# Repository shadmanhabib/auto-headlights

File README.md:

# Auto-Headlights
Controller designed to control and automate vehicle headlights based on environmental conditions in parallel with vehicle controls.

## Table of Contents
- [Auto-Headlights](#Auto-Headlights)
  - [Table of Contents](#table-of-contents)
  - [About The Project](#about-the-project)
  - [Getting Started](#getting-started)
    - [Prerequisites](#prerequisites)
    - [Installation](#installation)
  - [Usage](#usage)
  - [Changelog](#changelog)

## About The Project
This project was designed for a Subaru Liberty/Legacy 4GEN in an effort to add modern automatic headlights and light home functionalities.

It involves PCB design and automotive wiring. Hence, this project should only be replicated by individuals who are confident with automotive electrical systems.

The design was based around the following requirements:

1. Control headlights dependent on light conditions.
2. Ensure original vehicle controls remained functional.
3. Support reading lock/unlock states.
4. Ability to update software i.e. ensure programing pins are accessible through header/connector.

## Getting Started
To get a build this project (or parts thereof), these steps may be followed.

### Prerequisites
1. PlatformIO is required to build binaries from source code. Microchip Studios or Arduino IDE can also be used but will require extra configuration.
2. An ISP programmer is required to upload to the controller. An Arduino as ISP can be used.
3. If you want to make changes to the PCB design or would like to generate new fabrication files, an installation of KiCAD is required.
4. A 3D printer is required to fabricate the PCB enclosure from the provided CAD files.

### Installation
1. Manufacture and assemble controller PCB.
2. Build and upload code binary.
3. Fabricate PCB enclosure.
4. Splice vehicle wiring as per wiring diragram/requirements.
5. Pin connectors and attach to controller.
6. Mount controller in a secure location.

## Usage
Examples will be given in future iterations of this file.

_For more examples, please refer to the [Documentation](https://)_

## Changelog
All notable changes to this project will be documented in this section.

The format is based on [Keep a Changelog](https://keepachangelog.com/en/1.0.0/),
and this project attempts to adhere to [Semantic Versioning](https://semver.org/spec/v2.0.0.html).

### [v1.0.0]
#### Initial design
- ATmega328PB based design.
- Included optocouplers to read 12V signals from vehicle.
- MOLEX Micro-fit connectors.

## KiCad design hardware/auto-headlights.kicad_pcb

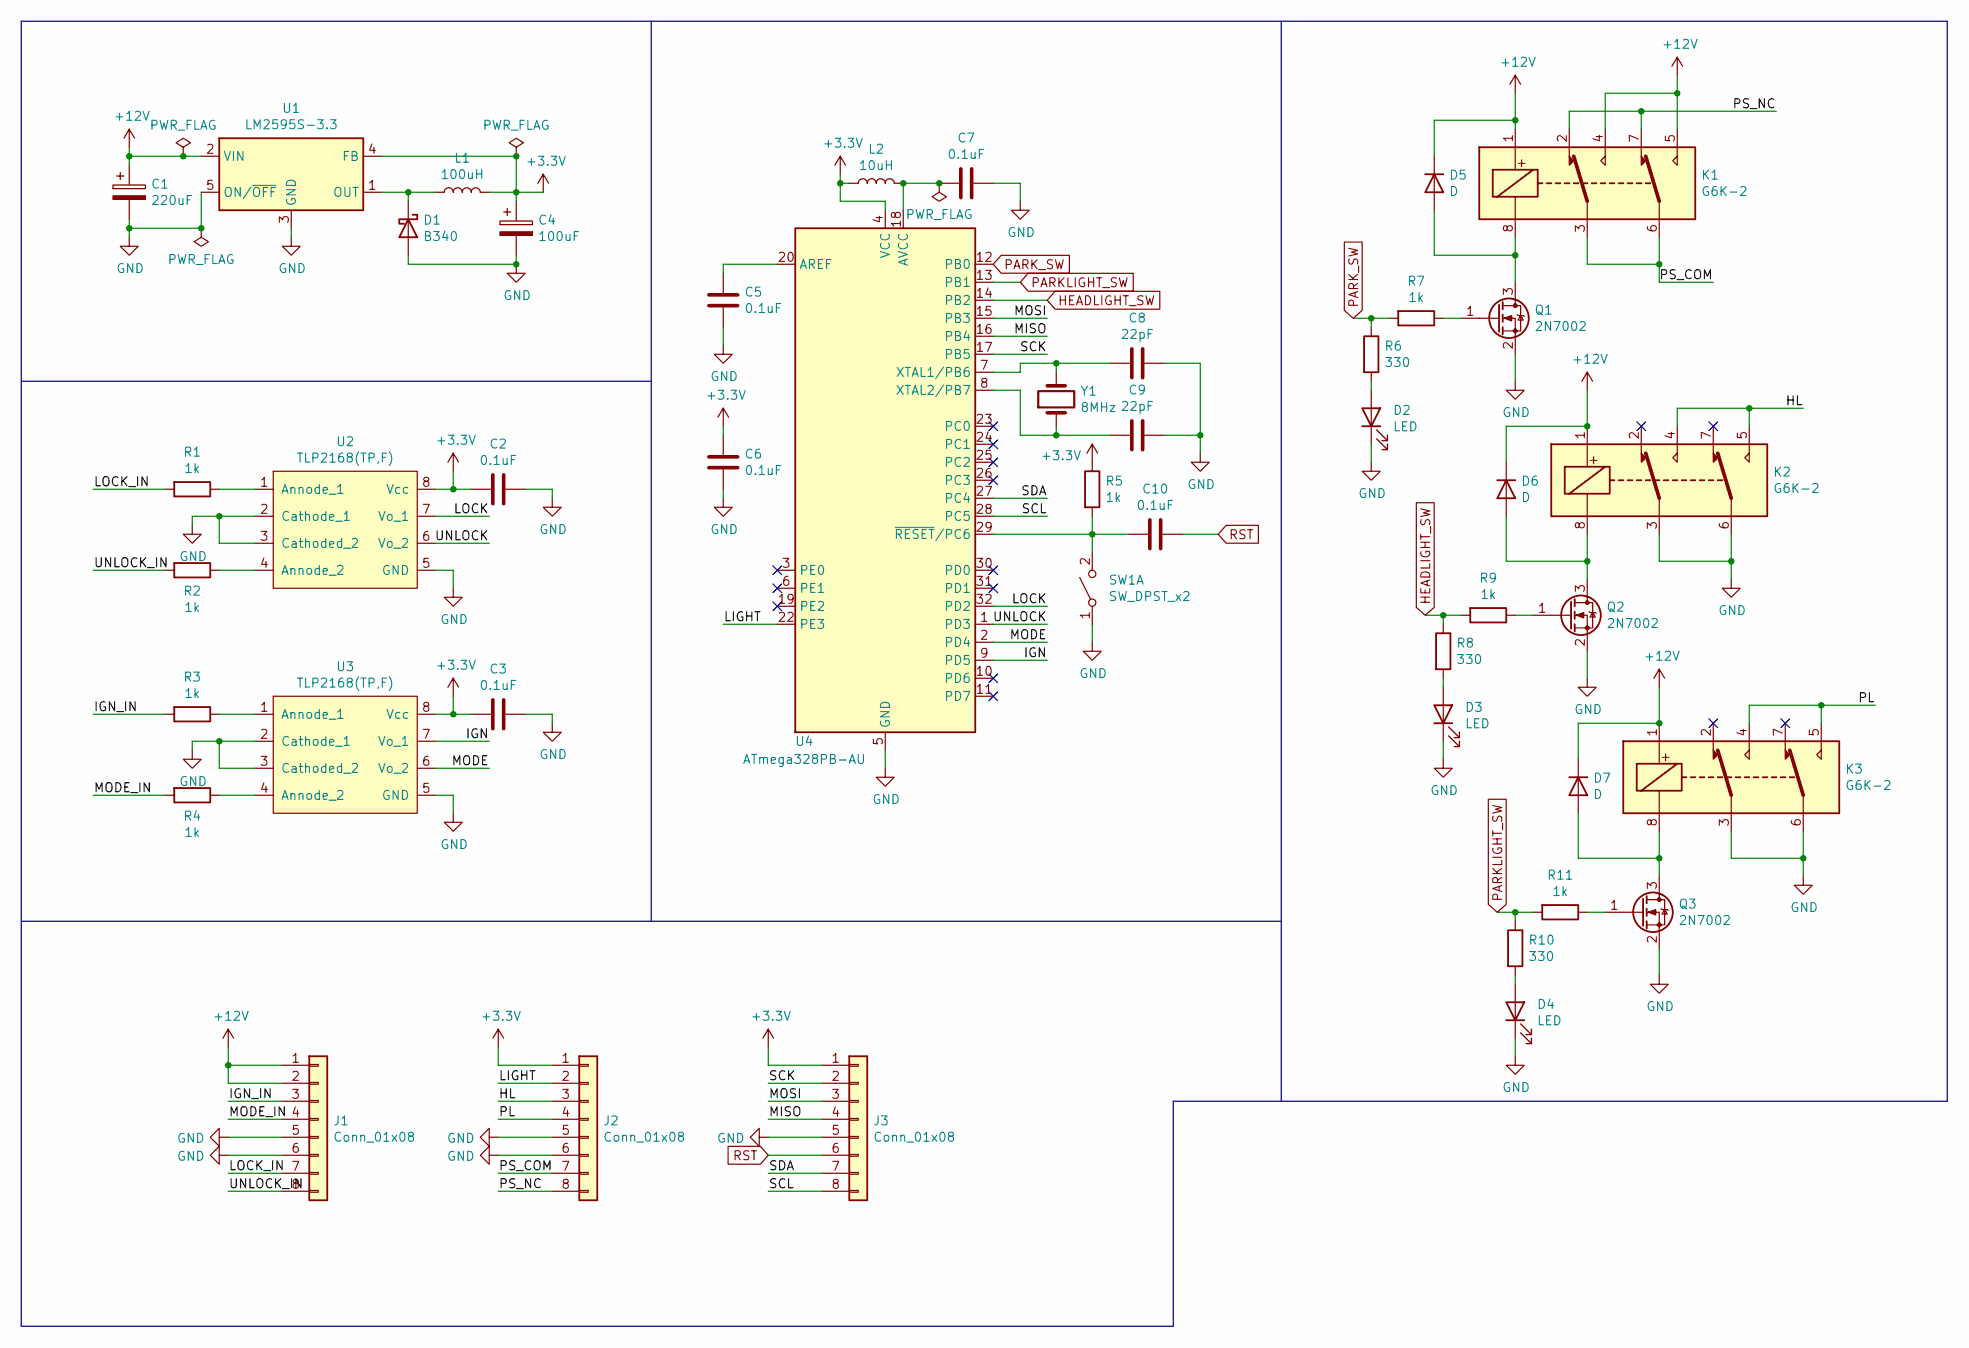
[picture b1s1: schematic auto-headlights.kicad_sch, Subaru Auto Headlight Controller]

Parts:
C1: 220uF; CP_EIA-7343-31_Kemet-D
C2, C3, C5, C6, C7, C10: 0.1uF; C_0805_2012Metric
C4: 100uF; CP_EIA-3528-21_Kemet-B
C8, C9: 22pF; C_0805_2012Metric
D1: B340; D_SOD-123
D2, D3, D4: LED; LED_0805_2012Metric_Castellated
D5, D6, D7: D; D_SOD-123
J1, J2, J3: Conn_01x08; Molex_Micro-Fit_3.0_43045-0812_2x04_P3.00mm_Vertical
K1, K2, K3: G6K-2; Relay_DPDT_Omron_G6K-2F-Y
L1: 100uH; L_0805_2012Metric
L2: 10uH; L_0805_2012Metric
Q1, Q2, Q3: 2N7002; SOT-23
R1, R2, R3, R4, R5, R7, R9, R11: 1k; R_0805_2012Metric
R6, R8, R10: 330; R_0805_2012Metric
SW1: SW_DPST_x2; SW_SPST_Omron_B3FS-100xP
U1: LM2595S-3.3; TO-263-5_TabPin3
U2, U3: TLP2168(TP,F); SO-8_3.9x4.9mm_P1.27mm
U4: ATmega328PB-AU; TQFP-32_7x7mm_P0.8mm
Y1: 8MHz; Crystal_SMD_5032-2Pin_5.0x3.2mm

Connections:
+3V3: C2.2, C3.2, C4.1, C6.1, J2.1, J3.1, L1.2, L2.1, R5.1, U1.4 (FB), U2.8 (Vcc), U3.8 (Vcc), U4.4 (VCC)
+12V: C1.1, D5.1 (K), D6.1 (K), D7.1 (K), J1.1, J1.2, K1.1, K1.4, K1.5, K2.1, K3.1, U1.2 (VIN)
/HL: J2.3, K2.4, K2.5
/IGN: U3.7 (Vo_1), U4.9 (PD5)
/IGN_IN: J1.3, R3.2
/LIGHT: J2.2, U4.22 (PE3)
/LOCK: U2.7 (Vo_1), U4.32 (PD2)
/LOCK_IN: J1.7, R1.2
/MISO: J3.4, U4.16 (PB4)
/MODE: U3.6 (Vo_2), U4.2 (PD4)
/MODE_IN: J1.4, R4.2
/MOSI: J3.3, U4.15 (PB3)
/PL: J2.4, K3.4, K3.5
/PS_COM: J2.7, K1.3, K1.6
/PS_NC: J2.8, K1.2, K1.7
/SCK: J3.2, U4.17 (PB5)
/SCL: J3.8, U4.28 (PC5)
/SDA: J3.7, U4.27 (PC4)
/UNLOCK: U2.6 (Vo_2), U4.1 (PD3)
/UNLOCK_IN: J1.8, R2.2
GND: C1.2, C2.1, C3.1, C4.2, C5.2, C6.2, C7.1, C8.1, C9.1, D1.2 (A), D2.1 (K), D3.1 (K), D4.1 (K), J1.5, J1.6, J2.5, J2.6, J3.5, K2.3, K2.6, K3.3, K3.6, Q1.2 (S), Q2.2 (S), Q3.2 (S), SW1.1 (A), U1.3 (GND), U1.5 (ON/~OFF), U2.2 (Cathode_1), U2.3 (Cathoded_2), U2.5 (GND), U3.2 (Cathode_1), U3.3 (Cathoded_2), U3.5 (GND), U4.5 (GND), U4.21 (GND)
HEADLIGHT_SW: R8.1, R9.2, U4.14 (PB2)
unnamed: C5.1, U4.20 (AREF)
unnamed: C7.2, L2.2, U4.18 (AVCC)
unnamed: C8.2, U4.7 (XTAL1/PB6), Y1.2
unnamed: C9.2, U4.8 (XTAL2/PB7), Y1.1
unnamed: C10.2, R5.2, SW1.2 (B), U4.29 (~RESET/PC6)
unnamed: D1.1 (K), L1.1, U1.1 (OUT)
unnamed: D2.2 (A), R6.2
unnamed: D3.2 (A), R8.2
unnamed: D4.2 (A), R10.2
unnamed: D5.2 (A), K1.8, Q1.3 (D)
unnamed: D6.2 (A), K2.8, Q2.3 (D)
unnamed: D7.2 (A), K3.8, Q3.3 (D)
unnamed: Q1.1 (G), R7.1
unnamed: Q2.1 (G), R9.1
unnamed: Q3.1 (G), R11.1
unnamed: R1.1, U2.1 (Annode_1)
unnamed: R2.1, U2.4 (Annode_2)
unnamed: R3.1, U3.1 (Annode_1)
unnamed: R4.1, U3.4 (Annode_2)
PARKLIGHT_SW: R10.1, R11.2, U4.13 (PB1)
PARK_SW: R6.1, R7.2, U4.12 (PB0)
RST: C10.1, J3.6

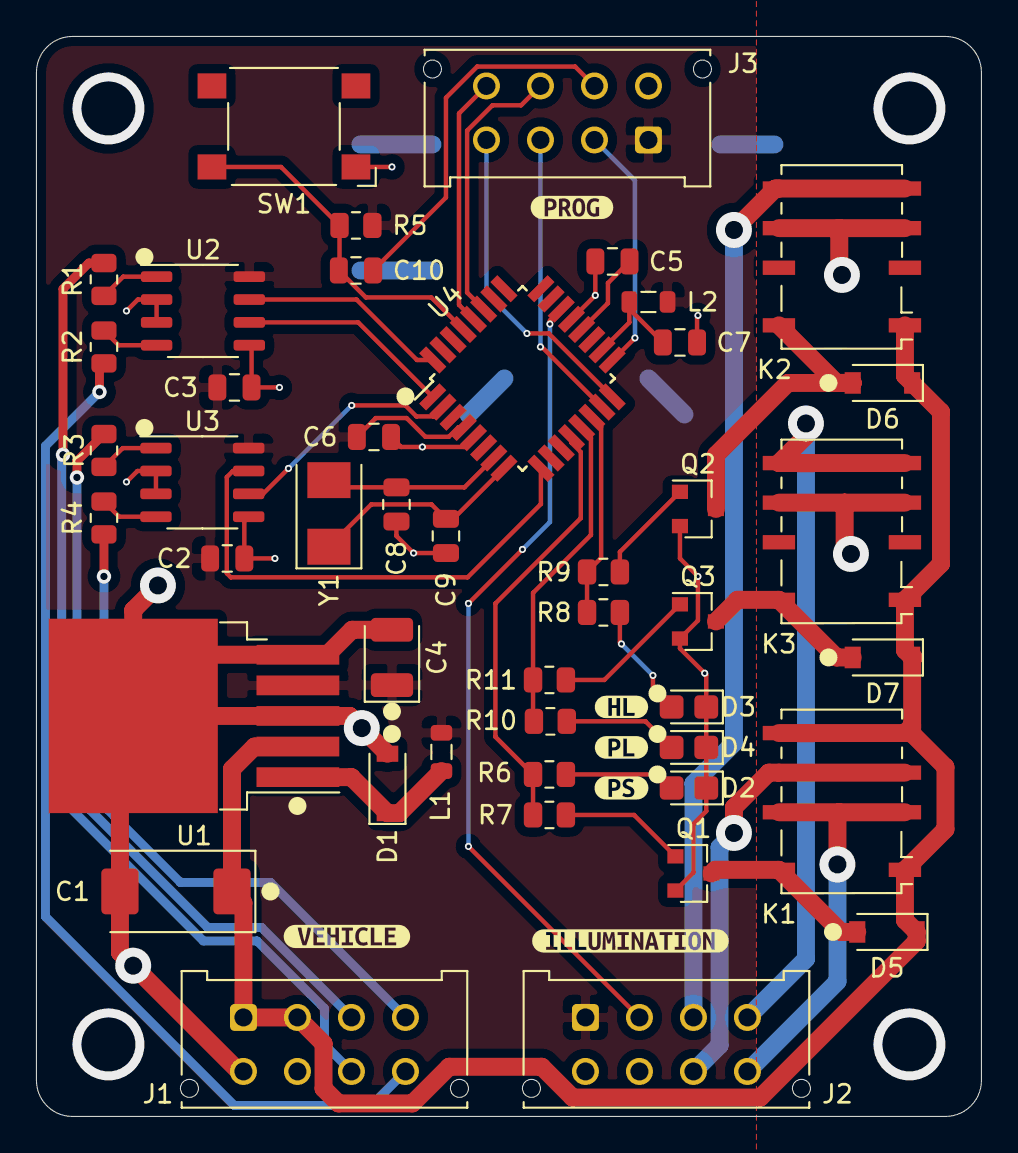
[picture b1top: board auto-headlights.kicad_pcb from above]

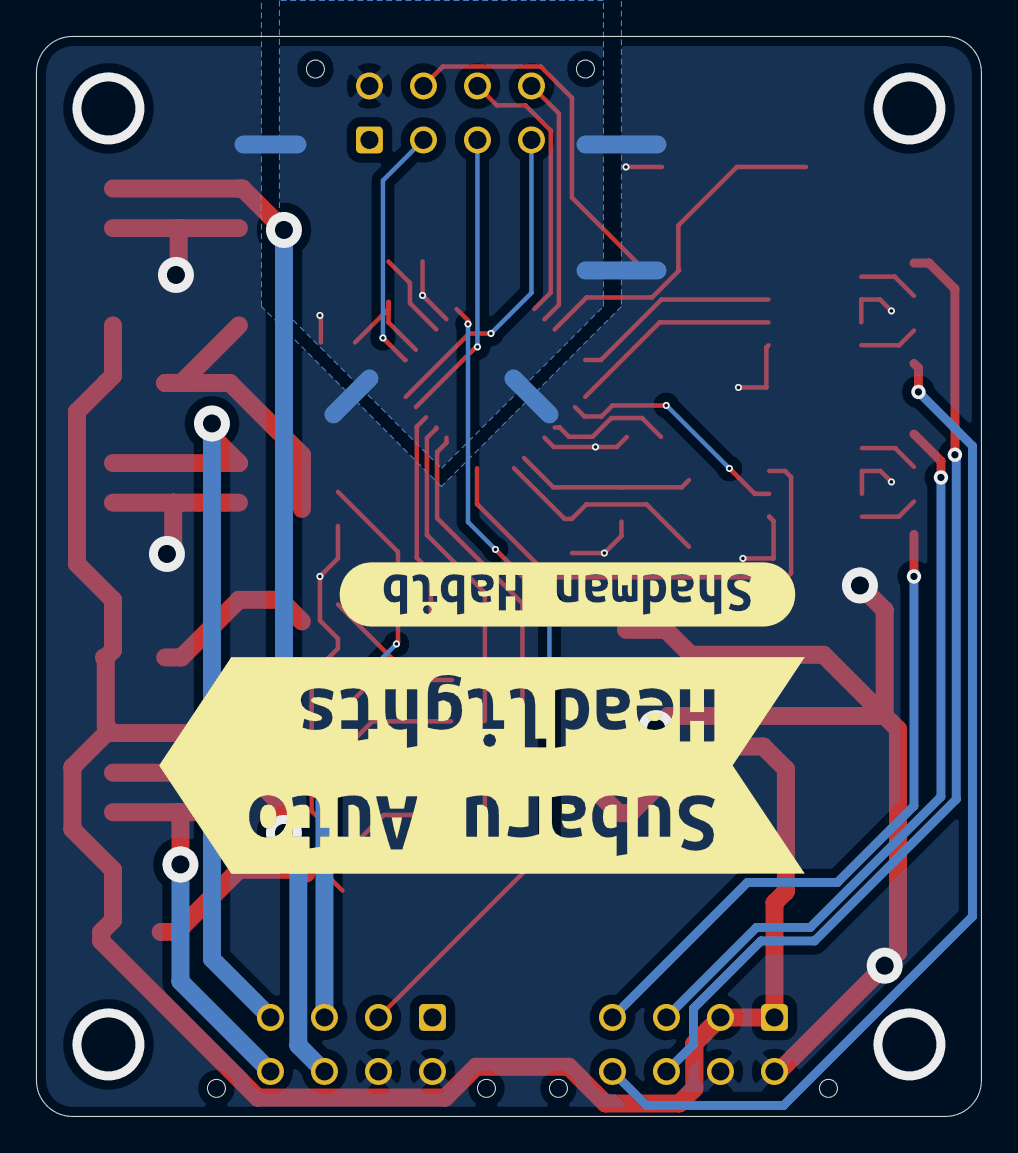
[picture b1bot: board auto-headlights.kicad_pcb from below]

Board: 2 copper layers, 52.5 x 60.0 mm, 53 parts (2 on the bottom side), 44 nets.

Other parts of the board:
kibuzzard-612DA6C3, kibuzzard-612DA6E7, kibuzzard-612DA7BB, kibuzzard-612DA65A, kibuzzard-612DA66E, kibuzzard-612DA640, kibuzzard-612DA714, kibuzzard-612DA797: G***; label

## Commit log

2024-01-06 added vscode extensions file
2024-01-06 added hardware and CAD to file structure
2024-01-07 additions to code
2024-01-08 added code for light home feature
2024-01-08 updated light home logic
2024-01-08 added sleep functionality
2024-01-10 updated interrupt logic and light functions
2024-01-10 added project README file
2024-01-10 import files
2024-01-11 Case version 2
2024-01-18 Bug fix
2024-01-18 Updated version info
